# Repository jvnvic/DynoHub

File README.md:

# DynoHub - Automotive Development Platform

DynoHub is an ESP32-based development board in an Arduino Uno form factor, designed for automotive applications. It was developed at the Elektroniklabor F107 for the Fachhochschule Dortmund.

## Features

- **ESP32 WROOM** – Integrated WiFi and Bluetooth
- **Modular Automotive-grade power supply** – Wide input voltage range: 4.75V to 45V
- **CAN Bus** – Automotive communication support
- **100Mbit Ethernet** – High-speed wired networking
- **MicroSD Card Slot** – Expandable storage
- **Arduino Shield Compatibility** – Supports most Arduino shields
- **Stackable Design** – Multiple boards can be stacked and bridged with a single power and CAN input

## Getting Started

DynoHub is beginner-friendly and easy to set up. An **Arduino IDE Board Configuration** is available, along with dedicated **libraries** for each peripheral, complete with example sketches.

### Installing the DynoHub Board Package in Arduino IDE

To use the DynoHub board with Arduino IDE, you need to install the custom board package. Follow these steps:

1. Open **Arduino IDE**.
2. Go to **File** > **Preferences** (Windows) or **Arduino** > **Preferences** (Mac).
3. In the **Additional Board Manager URLs** field, add the following URL:

```text
https://raw.githubusercontent.com/jvnvic/DynoHub/refs/heads/main/Software/arduino-esp32-dynohub/hardware/FH%20Dortmund/package_dynohub_index.json
```

  If there are existing URLs, separate them with a comma.

5. Click **OK** to save the settings.
6. Open **Tools** > **Board** > **Boards Manager**.
7. Search for **DynoHub** and install the corresponding board package.
8. Once installed, select the appropriate **DynoHub** board from **Tools** > **Board**.

You are now ready to program your DynoHub board with Arduino IDE!

### Libraries & Examples
Libraries are available for:
- Ethernet: https://github.com/jvnvic/UDPSender
- SD Card: https://github.com/jvnvic/EasySDMMC

Each library comes with sample code to help you get started quickly.

## Diagrams

- **Pinout Diagram**  

- **Functional Schematic Block Diagram**  
  
## License
This project is open-source and available for personal and educational use.

---

Developed at **Elektroniklabor F107** – **Fachhochschule Dortmund**

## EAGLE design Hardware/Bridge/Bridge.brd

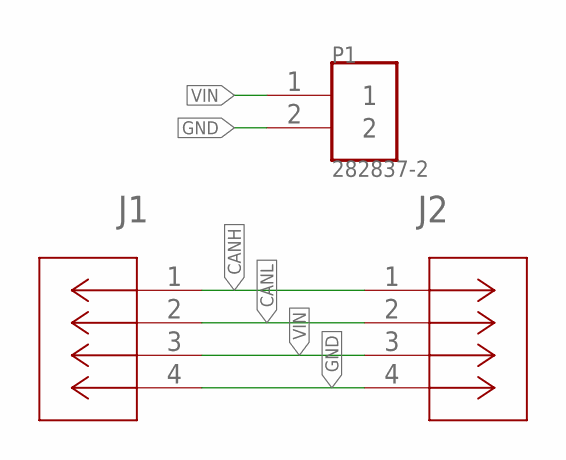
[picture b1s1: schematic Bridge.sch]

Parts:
J1, J2: 22027043CONN4X1_22027043_MOL; CONN4X1_22027043_MOL
P1: 282837-2; TE_282837-2

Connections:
CANH: J1.1, J2.1
CANL: J1.2, J2.2
GND: J1.4, J2.4, P1.2
VIN: J1.3, J2.3, P1.1

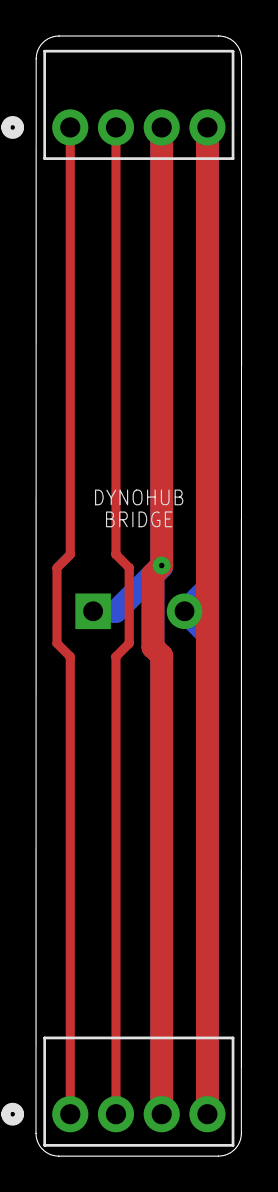
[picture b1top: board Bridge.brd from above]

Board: 2 copper layers, 11.4 x 62.2 mm, 3 parts (1 on the bottom side), 4 nets.

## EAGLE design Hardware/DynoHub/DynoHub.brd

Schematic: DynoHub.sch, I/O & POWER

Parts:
3.3V, 5V, 12V: C965807; CHIPLED_0603
C1, C4: 1uF; C0603
C2, C6, C7, C9, C20, C22, C29, C30, C33, C34, C35: 100nF; C0402K
C3: 4.7uF; C0402K
C5: 47uF; C0805
C8: 2.2uF; C0402K
C10, C103: 100 nF; C0402K
C19: 4.7uF; C0603
C21, C43: 1nF; C0402K
C23, C24: 22uF; C0603
C27, C28, C31, C32: 100nF; C0603
C107: 4.7nF 100V; C0603
C108, C109: 100pF 50V; C0603
CAN_TX: SJ
D6: BAT54C; SOT95P240X120-3N
D7: ESDS314DBVR; SOT95P280X145-5N
D8, D9: GG0402052R542P; DIONC1006X55N
D101: NUP2105LT1G; SOT96P237X111-3N
ETH_EN: SJ
F1: MF-FSML050_8-2; FUSC1608X70N
IC1: LMV321AIDBVR; SOT95P280X145-5N
IC2, IC6, IC7: TXB0108DQSR
IC3: USBLC6-2SC6; SOT95P280X145-6N
IC4: TLV1117LV33DCYR; SOT230P700X180-4N
IC9: ESP32-WROOM-32E-N8R2; ESP32WROOM32EN8R2
IC10: CP2102N-A02-GQFN28R; QFN50P500X500X80-29N
IC11: TS3L501ERUAR; QFN50P350X900X80-43N
J4: TYPE-C-31-M-12; HRO_TYPE-C-31-M-12
J5, J6: 1718570004CONN_SD-171857-0001_M265_04_MO; CONN_SD-171857-0001_M265_04_MO
J9: HR911105A; HANRUN_HR911105A
J-SD_DAT: SJ
JANALOG1: 6x1F-H8.5-L14.5mm; 1X06
JHIGH1: 10x1F-H8.5-L14.5mm; 1X10
JLOW1: 8x1F-H8.5-L14.5mm; 1X08
J_SD_CLK: SJ
J_SD_CMD: SJ
L1, L5: 600R 2A; L2012C
MICRO_SD1: TF-01A
POWER1: 8x1F-H8.5-L14.5mm; 1X08
Q1, Q2: SS8050-G; SOT95P240X115-3N
Q3: FDN340P; SOT95P237X112-3N
R1: 1M; R0603
R2, R3: 5K1; R0603
R4, R18, R19, R20, R28, R32, R49, R50, R51, R52, R57, R58: 2.2k; R0402
R5, R8, R29, R31, R35: 10k; R0603
R6: 47.5k 5%; R0402
R9: 470; R0603
R10: 22.1k 5%; R0402
R11: 100; R0603
R12: 15; R0603
R13: 2k 5%; R0402
R14, R15, R16: 10k 5%; R0402
R17, R22: 220; R0402
R21: 10; R0402
R23, R30, R55: 10k; R0402
R24, R25, R26, R27: 49,9 1%; R0402
R53, R54: 2.2k; R0603
R56: 12k 1%; R0402
R104: 47K; R0603
R107, R108: 59; R0603
R111: 10K; R0402
S3: EVP-AF5B70; EVPAF5B70
SJ1: SJ
U2: LAN8710A-EZC; QFN50P500X500X100-33N
U3: SN65HVD230; SOIC127P599X175-8N
U$1, U$2, U$3, U$4, U$5, U$6, U$7, U$13, U$14, U$15, U$16, U$17, U$18, U$19, U$20, U$21, U$22, U$23, U$24, U$25, U$26, U$27, U$28, U$29, U$30, U$31, U$32, U$33, U$34, U$35: NC
U$8, U$9, U$10, U$11, U$12: 2X3MM_PAD
Z1: BZX384C5V1-HE3-08; SOD2713X115N

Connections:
3V3: 3.3V.A, C2.1, C3.1, C4.1, C19.1, C20.1, C22.1, C23.1, C27.2, C29.2, C31.2, C35.2, C103.1, ETH_EN.1, IC1.4 (-IN), IC2.5 (VCCA), IC4.2 (OUTPUT_1), IC4.4 (OUTPUT_2), IC6.5 (VCCA), IC7.5 (VCCA), IC9.2 (3V3), IC10.6 (VDD), IC10.7 (VREGIN), IC11.39 (VDD_7), J9.9 (GA), L1.1, L5.1, POWER1.4, R4.2, R13.1, R18.2, R19.2, R20.2, R23.2, R28.2, R51.2, R52.2, R53.2, R54.2, R55.2, R111.2, U2.12 (VDDIO), U3.3 (VCC)
5V: 5V.A, C1.1, C28.2, C30.2, C32.2, IC1.5 (V+), IC2.16 (VCCB), IC4.3 (INPUT), IC6.16 (VCCB), IC7.16 (VCCB), POWER1.2, POWER1.5, Q3.2 (S), U$8.P$1
12V: 12V.A, POWER1.8, R8.2, U$9.P$1
!ETH_EN: ETH_EN.2, IC11.13 (SEL), R35.2
A0/ADC1_6/GPIO34: IC7.10 (A8), IC9.6 (IO34)
A0/ADC1_6/GPIO34_5V: IC7.11 (B8), JANALOG1.1
A1/ADC1_7/GPIO35: IC7.9 (A7), IC9.7 (IO35)
A1/ADC1_7/GPIO35_5V: IC7.12 (B7), JANALOG1.2
A2/ADC1_4/GPIO32: IC7.8 (A6), IC9.8 (IO32)
A2/ADC1_4/GPIO32_5V: IC7.13 (B6), JANALOG1.3
A3/ADC1_5/GPIO33: IC7.7 (A5), IC9.9 (IO33)
A3/ADC1_5/GPIO33_5V: IC7.14 (B5), JANALOG1.4
A4/TXCAN/ADC2_0/GPIO4: CAN_TX.1, IC7.4 (A4), IC9.26 (IO4)
A4/TXCAN/ADC2_0/GPIO4_5V: IC7.17 (B4), JANALOG1.5
A5/ADC2_2/SD_DAT0/GPIO2: D6.1 (A1), IC7.3 (A3), IC9.24 (IO2), J-SD_DAT.1
A5/ADC2_2/SD_DATO/GPIO2_5V: IC7.18 (B3), JANALOG1.6
AREF/GPI39: IC9.5 (SENSOR_VN), JHIGH1.8
CANGND_BF_C: C107.2, SJ1.1
CANH_P: C109.2, D101.2 (A_2), J5.4, J6.4, R108.1, U3.7 (CANH)
CANL_BF_JMP: R107.1, R108.2, SJ1.2
CANL_N: C108.2, D101.1 (A_1), J5.3, J6.3, R107.2, U3.6 (CANL)
CC1: J4.A5 (CC1), R3.2
CC2: J4.B5 (CC2), R2.2
CLK: MICRO_SD1.5 (CLK), R22.1
CMP: IC1.3 (+IN), R5.2, R8.1, Z1.1 (K)
CS/D10/GPIO5: IC6.8 (A6), IC9.29 (IO5)
CS/D10/GPIO5_5V: IC6.13 (B6), JHIGH1.3
D0/UART_RXD: IC2.10 (A8), IC9.34 (RXD0), IC10.25 (RXD)
D0/UART_RXD_5V: IC2.11 (B8), JLOW1.1
D1/UART_TXD: IC2.9 (A7), IC9.35 (TXD0), IC10.26 (TXD)
D1/UART_TXD_5V: IC2.12 (B7), JLOW1.2
D2/EMAC_RXD1/GPIO26: IC9.11 (IO26), IC11.3 (A1)
D2/GPIO26: IC2.8 (A6), IC11.35 (C1)
D2/GPIO26_5V: IC2.13 (B6), JLOW1.3
D3/EMAC_RXD0/GPIO25: IC9.10 (IO25), IC11.6 (A2)
D3/GPIO25: IC2.7 (A5), IC11.32 (C2)
D3/GPIO25_5V: IC2.14 (B5), JLOW1.4
D4/EMAC_CO180/GPIO17: IC9.28 (IO17), IC11.2 (A0)
D4/GPIO17: IC2.4 (A4), IC11.36 (C0)
D4/GPIO17_5V: IC2.17 (B4), JLOW1.5
D5/GPIO16: IC2.3 (A3), IC9.27 (IO16)
D5/GPIO16_5V: IC2.18 (B3), JLOW1.6
D6/EMAC_RX_CRS_DV/GPIO27: IC9.12 (IO27), IC11.7 (A3)
D6/GPIO27: IC2.2 (A2), IC11.31 (C3)
D6/GPIO27_5V: IC2.19 (B2), JLOW1.7
D7/SD_CLK/GPIO14: IC2.1 (A1), IC9.13 (IO14), J_SD_CLK.1
D7/SD_CLK/GPIO14_5V: IC2.20 (B1), JLOW1.8
D8/GPIO12: IC6.10 (A8), IC9.14 (IO12)
D8/GPIO12_5V: IC6.11 (B8), JHIGH1.1
D9/GPIO13: IC6.9 (A7), IC9.16 (IO13)
D9/GPIO13_5V: IC6.12 (B7), JHIGH1.2
DAT0: MICRO_SD1.7 (DAT0), R21.1
DAT1: MICRO_SD1.8 (DAT1), R4.1
DAT2: MICRO_SD1.1 (DAT2), R20.1
DAT3: MICRO_SD1.2 (CD/DAT3), R19.1
EMAC_CO180: IC11.38 (B0), U2.5 (XTAL1/CLKIN)
EMAC_MDC: IC11.28 (B5), U2.17 (MDC)
EMAC_MDIO: IC11.29 (B4), R53.1, U2.16 (MDIO)
EMAC_RXD0: IC11.34 (B2), R51.1, U2.11 (RXD0/MODE0)
EMAC_RXD1: IC11.37 (B1), R52.1, U2.10 (RXD1/MODE1)
EMAC_RX_CRS_DV: IC11.33 (B3), R54.1, U2.15 (COL/CRS_DV/MODE2)
EMAC_TXD0: IC11.24 (B7), U2.22 (TXD0)
EMAC_TXD1: IC11.17 (LED__B0), U2.23 (TXD1)
EMAC_TX_EN: IC11.25 (B6), U2.21 (TXEN)
ESP_EN: C6.1, C10.1, IC9.3 (EN), POWER1.3, Q1.3 (C), R111.1, S3.A1 (NO_1), S3.A2 (NO_2)
ETH_LED_G: J9.10 (GC), R57.2
ETH_LED_Y: J9.12 (YA), R58.2
ETH_VDDCR: C7.1, C8.1, U2.6 (VDDCR)
GND: C1.2, C2.2, C3.2, C4.2, C5.1, C6.2, C7.2, C8.2, C9.2, C10.2, C19.2, C20.2, C21.2, C22.2, C23.2, C24.2, C27.1, C28.1, C29.1, C30.1, C31.1, C32.1, C33.2, C34.2, C35.1, C43.2, C103.2, C107.1, C108.1, C109.1, D7.2 (GND), D101.3 (A_3), IC1.2 (V-), IC2.15 (GND), IC3.2 (GND), IC4.1 (GND), IC6.15 (GND), IC7.15 (GND), IC9.1 (GND_1), IC9.15 (GND_2), IC9.38 (GND_3), IC9.39 (GND_4), IC9.40 (GND_5), IC9.41 (GND_6), IC9.42 (GND_7), IC9.43 (GND_8), IC9.44 (GND_9), IC9.45 (GND_10), IC9.46 (GND_11), IC9.47 (GND_12), IC10.3 (GND_1), IC10.29 (GND_2), IC11.5 (PD), IC11.43 (GND), J4.A1_B12 (GND), J4.B1_A12 (GND), J5.1, J6.1, J9.8 (GND), J9.11 (YC), JHIGH1.7, MICRO_SD1.6 (VSS), MICRO_SD1.MP1 (SHIELD), MICRO_SD1.MP2 (SHIELD), MICRO_SD1.MP3 (SHIELD), MICRO_SD1.MP4 (SHIELD), POWER1.6, POWER1.7, R1.1, R2.1, R3.1, R5.1, R6.1, R9.1, R11.1, R12.1, R14.1, R29.1, R30.1, R31.1, R32.2, R35.1, R49.2, R50.2, R56.1, R104.1, S3.B1 (COM_1), S3.B2 (COM_2), U2.24 (TXD2), U2.25 (TXD3), U2.33 (VSS), U3.2 (GND), U$11.P$1, U$12.P$1, Z1.2 (A)
GPIO0: D6.2 (A2), IC9.25 (IO0), Q2.3 (C), R17.2
MISO/D12/EMAC_TXD0/GPIO19: IC9.31 (IO19), IC11.12 (A7)
MISO/D12/GPIO19: IC6.4 (A4), IC11.22 (C7)
MISO/D12/GPIO19_5V: IC6.17 (B4), JHIGH1.5
MOSI/D11/EMAC_MDC/GPIO23: IC9.37 (IO23), IC11.10 (A5)
MOSI/D11/GPIO23: IC6.7 (A5), IC11.26 (C5)
MOSI/D11/GPIO23_5V: IC6.14 (B5), JHIGH1.4
unnamed: J4.S1 (SHIELD), J4.S2 (SHIELD), J4.S3 (SHIELD), J4.S4 (SHIELD), R1.2
unnamed: IC10.9 (RSTB), R13.2
unnamed: IC10.11 (SUSPENDB), R14.2
unnamed: Q1.1 (B), R16.1
unnamed: 12V.C, R9.2
unnamed: R104.2, U3.8 (RS)
unnamed: IC1.1 (OUT), Q3.1 (G)
unnamed: Q2.1 (B), R15.1
unnamed: D6.3 (CC), R17.1
unnamed: 5V.C, R11.2
unnamed: 3.3V.C, R12.2
unnamed: C21.1, J9.15 (SHIELD), J9.16 (SHIELD)
unnamed: F1.1, J4.A4_B9 (VBUS), J4.B4_A9 (VBUS)
unnamed: R28.1, U2.9 (RXD2/RMIISEL)
unnamed: R32.1, U2.8 (RXD3/PHYAD2)
unnamed: R49.1, U2.13 (RXER/RXD4/PHYAD0)
unnamed: R50.1, U2.7 (RXCLK/PHYAD1)
unnamed: C43.1, R55.1, U2.19 (NRST)
unnamed: R56.2, U2.32 (RBIAS)
unnamed: R58.1, U2.3 (LED1/REGOFF)
unnamed: R57.1, U2.2 (LED2/NINTSEL)
OE_A: IC2.6 (OE), R29.2
OE_B: IC6.6 (OE), R30.2
OE_C: IC7.6 (OE), R31.2
PC0: IC7.1 (A1)
PC0O: IC7.20 (B1)
PC1: IC7.2 (A2)
PC1O: IC7.19 (B2)
PHY_VDD: C9.1, C24.1, C33.1, C34.1, J9.4, J9.5, L5.2, R24.2, R25.2, R26.2, R27.2, U2.1 (VDD2A), U2.27 (VDD1A)
RXCAN/GPI36: IC9.4 (SENSOR_VP), U3.4 (R)
RX_N: D7.3 (I/O2), D9.1, J9.1 (TD+), R27.1, U2.30 (RXN)
RX_P: D7.1 (I/O1), D9.2, J9.3 (RD+), R25.1, U2.31 (RXP)
SCK/D13/EMAC_MDIO/GPIO18: IC9.30 (IO18), IC11.9 (A4)
SCK/D13/GPIO18: IC6.3 (A3), IC11.27 (C4)
SCK/D13/GPIO18_5V: IC6.18 (B3), JHIGH1.6
SCL/EMAC_TXD1/GPIO22: IC9.36 (IO22), IC11.15 (LED_A0)
SCL/GPIO22: IC6.1 (A1), IC11.19 (LED_C0)
SCL/GPIO22_5V: IC6.20 (B1), JHIGH1.10
SDA/EMAC_TX_EN/GPIO21: IC9.33 (IO21), IC11.11 (A6)
SDA/GPIO21: IC6.2 (A2), IC11.23 (C6)
SDA/GPIO21_5V: IC6.19 (B2), JHIGH1.9
SD_CLK/GPIO14_S: J_SD_CLK.2, R22.2
SD_CMD/GPIO15: IC9.23 (IO15), J_SD_CMD.1
SD_CMD/GPIO15_S: J_SD_CMD.2, MICRO_SD1.3 (CMD), R23.1
SD_DAT0/GPIO2_S: J-SD_DAT.2, R18.1, R21.2
TXCAN: CAN_TX.2, U3.1 (D)
TX_N: D7.4 (I/O3), D8.2, J9.2 (TD-), R26.1, U2.28 (TXN)
TX_P: D7.5 (I/O4), D8.1, J9.6 (RD-), R24.1, U2.29 (TXP)
USB_CTS: IC10.23 (CTS)
USB_DATA_CON_N: IC3.6 (I/O1_2), J4.A7 (DN1), J4.B7 (DN2)
USB_DATA_CON_P: IC3.4 (I/O2_2), J4.A6 (DP1), J4.B6 (DP2)
USB_DATA_N: IC3.1 (I/O1_1), IC10.5 (D-)
USB_DATA_P: IC3.3 (I/O2_1), IC10.4 (D+)
USB_DCD: IC10.1 (DCD)
USB_DSR: IC10.27 (DSR)
USB_DTR: IC10.28 (DTR), Q2.2 (E), R16.2
USB_RI: IC10.2 (RI_/_CLK)
USB_RTS: IC10.24 (RTS), Q1.2 (E), R15.2
VBUS: F1.2, IC3.5 (VBUS), IC10.8 (VBUS), Q3.3 (D), R6.2, R10.1, R10.2
VDD: C5.2, L1.2, MICRO_SD1.4 (VDD)
VIN: J5.2, J6.2, U$10.P$1

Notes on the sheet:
Auto program DTR RTS-->EN IO0 1 1 1 1 0 0 1 1 1 0 0 1 0 1 1 0
Pulldown OE nochmal prüfen
The PHY is set up as follows: MODE: All capable(10/100Base) -Auto-negotiation enabled -RMII Configuration -SMI address: 0x00
SEL
Function
A -> B
A -> C
Disconnect
Turn on S1 to deactivate Ethernet
limit cmp to 5.1V
7V-30V input

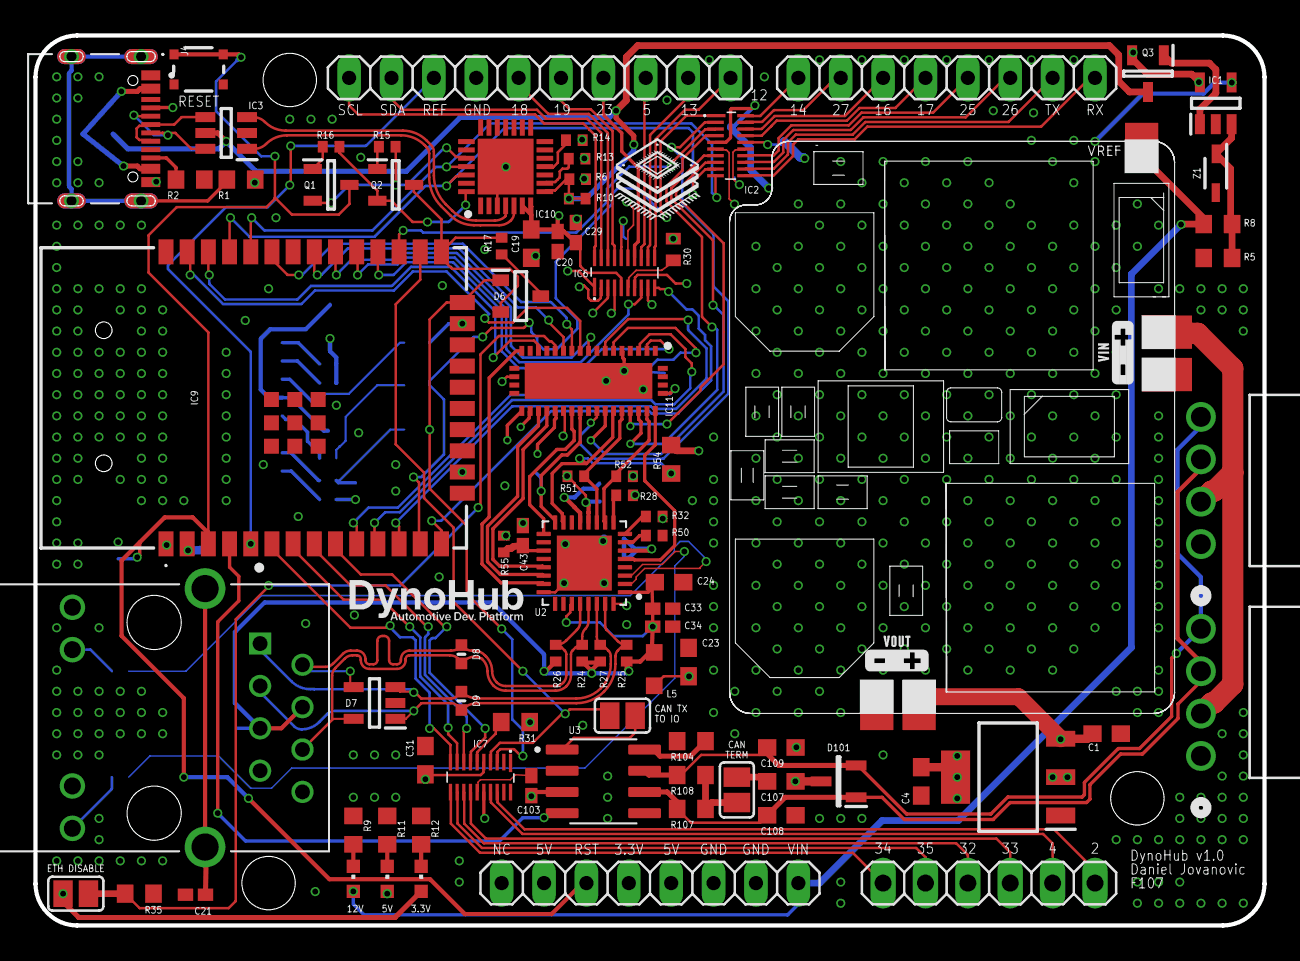
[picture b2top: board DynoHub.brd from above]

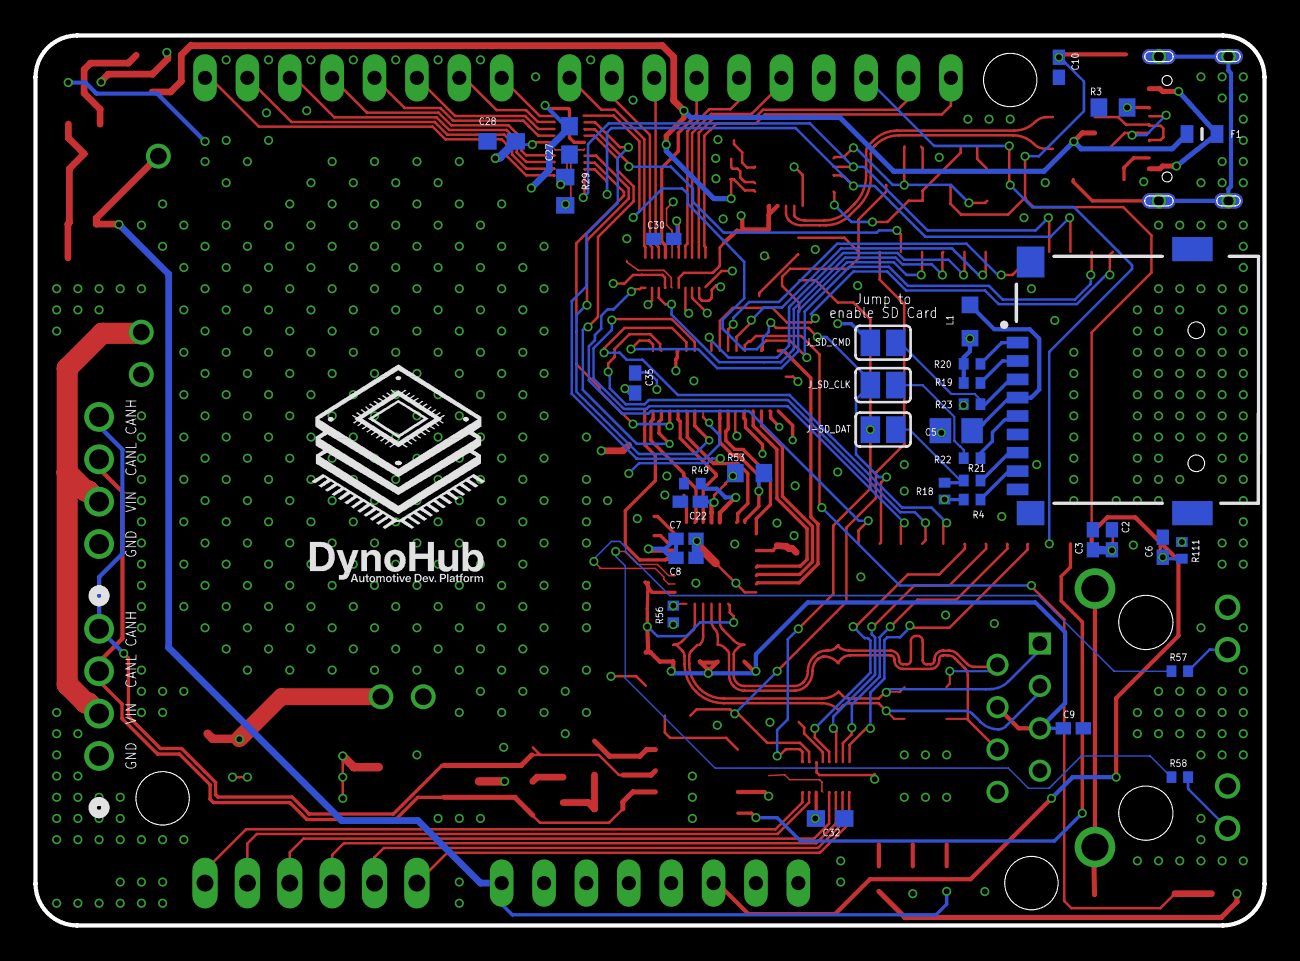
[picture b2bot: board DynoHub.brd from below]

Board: 4 copper layers, 73.7 x 53.3 mm, 153 parts (35 on the bottom side), 129 nets.

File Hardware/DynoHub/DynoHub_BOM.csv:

Comment,Designator,Footprint,LCSC Part #
1M,R1,R0603,C22935
1nF,C21 C43,C0402,C1523
1uF,C1 C4,C0603,C15849
2.2k,R28 R32 R50 R51 R52,R0402,C25879
2.2k,R54,R0603,C4190
2k 5%,R13,R0402,C4109
4.7nF 100V,C107,C0603,C12164
4.7uF,C19,C0603,C19666
5K1,R2,R0603,C23186
10k,R5 R8,R0603,C25804
10k,R30,R0402,C25744
10k,R31 R35,R0603,C25804
10k,R55,R0402,C25744
10k 5%,R14 R15 R16,R0402,C25744
15,R12,R0603,C22810
22.1k 5%,R10,R0402,C43473
22uF,C23 C24,C0603,C59461
47.5k 5%,R6,R0402,C25896
47K,R104,R0603,C25819
49 9 1%,R24,R0402,C25120
49 9 1%,R25,R0402,C25120
49 9 1%,R26,R0402,C25120
49 9 1%,R27,R0402,C25120
59,R107 R108,R0603,C23086
100,R11,R0603,C22775
100 nF,C103,C0402,C1525
100nF,C20 C29,C0402,C1525
100nF,C31,C0603,C14663
100nF,C33 C34,C0402,C1525
100pF 50V,C108 C109,C0603,C14858
220,R17,R0402,C25091
470,R9,R0603,C23179
600R 2A,L5,L2012C,C3716677
BAT54C,D6,SOT95P240X120-3N,C916424
BZX384C5V1-HE3-08,Z1,SOD2713X115N,C232203
C965807,3.3V 5V 12V,CHIPLED_0603,C965807
CP2102N-A02-GQFN28R,IC10,QFN50P500X500X80-29N,C964632
ESDS314DBVR,D7,SOT95P280X145-5N,C1847859
ESP32-WROOM-32E-N8R2,IC9,ESP32WROOM32EN8R2,C5361945
EVP-AF5B70,S3,EVPAF5B70,C79148
FDN340P,Q3,SOT95P237X112-3N,C75469
GG0402052R542P,D8 D9,DIONC1006X55N,C1973257
LAN8710A-EZC,U2,QFN50P500X500X100-33N,C46185
LMV321AIDBVR,IC1,SOT95P280X145-5N,C484730
NUP2105LT1G,D101,SOT96P237X111-3N,C2890118
SN65HVD230,U3,SOIC127P599X175-8N,C12084
SS8050-G,Q1 Q2,SOT95P240X115-3N,C164886
TLV1117LV33DCYR,IC4,SOT230P700X180-4N,C15578
TS3L501ERUAR,IC11,QFN50P350X900X80-43N,C2652454
TXB0108DQSR,IC2 IC6 IC7,TXB0108DQSR,C427057
TYPE-C-31-M-12,J4,HRO_TYPE-C-31-M-12,C165948
USBLC6-2SC6,IC3,SOT95P280X145-6N,C7519
2.2k,R4 R18 R19 R20 R49,R0402,C25879
2.2k,R53,R0603,C4190
2.2k,R57 R58,R0402,C25879
2.2uF,C8,C0402,C12530
4.7uF,C3,C0402,C23733
5K1,R3,R0603,C23186
10,R21,R0402,C25077
10K,R111,R0402,C25744
10k,R23,R0402,C25744
10k,R29,R0603,C25804
12k 1%,R56,R0402,C25752
47uF,C5,C0805,C16780
100 nF,C10,C0402,C1525
100nF,C2 C6 C7 C9 C22,C0402,C1525
100nF,C27 C28,C0603,C14663
100nF,C30,C0402,C1525
100nF,C32,C0603,C14663
100nF,C35,C0402,C1525
220,R22,R0402,C25091
600R 2A,L1,L2012C,C3716677
MF-FSML050_8-2,F1,FUSC1608X70N,C2844464
TF-01A,MICRO_SD1,TF-01A,C91145
HR911105A,LAN,HR911105A,C12074

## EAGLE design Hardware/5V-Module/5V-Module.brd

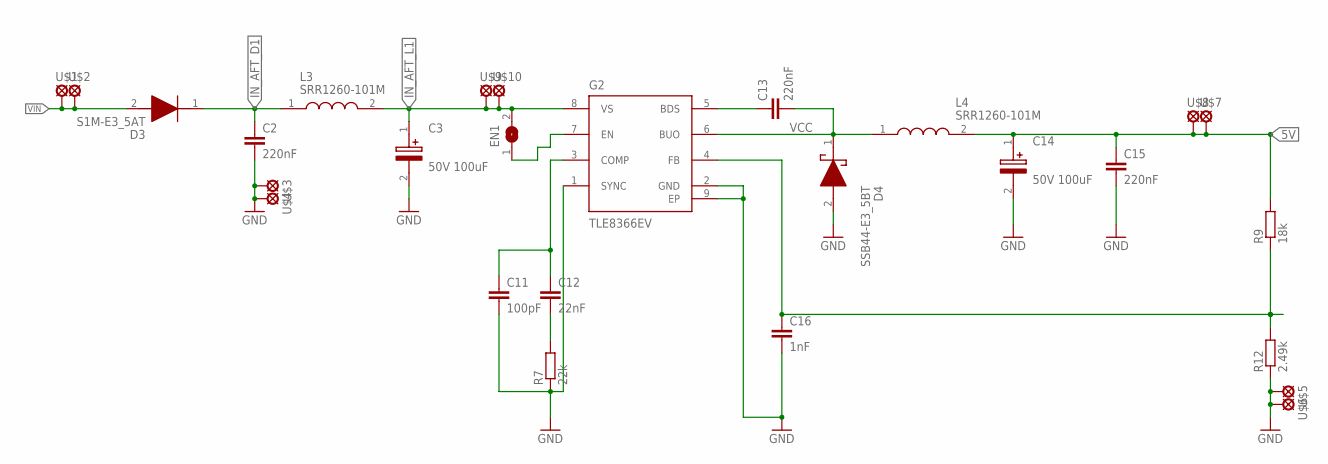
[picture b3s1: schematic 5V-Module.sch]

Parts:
C2, C13, C15: 220nF; C0603
C3, C14: 50V 100uF; CAPAE830X1050N
C11: 100pF; C0603
C12: 22nF; C0603
C16: 1nF; C0603
D3: S1M-E3_5AT; DIOM5127X229N
D4: SSB44-E3_5BT; DIOM5436X244N
EN1: SJ
G2: TLE8366EV; SOIC127P600X170-9N-1
L3, L4: SRR1260-101M; SRR1260101M
R7: 22k; R0603
R9: 18k; R0603
R12: 2.49k; R0603
U$1, U$2, U$3, U$4, U$5, U$6, U$7, U$8, U$9, U$10: 2MM_PAD

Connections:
5V: C14.1 (+), C15.1, L4.2, R9.2, U$7.P$1, U$8.P$1
GND: C2.2, C3.2 (-), C11.2, C14.2 (-), C15.2, C16.2, D4.2 (A), G2.1 (SYNC), G2.2 (GND), G2.9 (EP), R7.1, R12.1, U$3.P$1, U$4.P$1, U$5.P$1, U$6.P$1
IN_AFT_D1: C2.1, D3.1 (K), L3.1
IN_AFT_L1: C3.1 (+), EN1.2, G2.8 (VS), L3.2, U$9.P$1, U$10.P$1
unnamed: C11.1, C12.1, G2.3 (COMP)
unnamed: C12.2, R7.2
unnamed: C13.1, G2.5 (BDS)
unnamed: C16.1, G2.4 (FB), R9.1, R12.2
unnamed: EN1.1, G2.7 (EN)
VCC: C13.2, D4.1 (K), G2.6 (BUO), L4.1
VIN: D3.2 (A), U$1.P$1, U$2.P$1

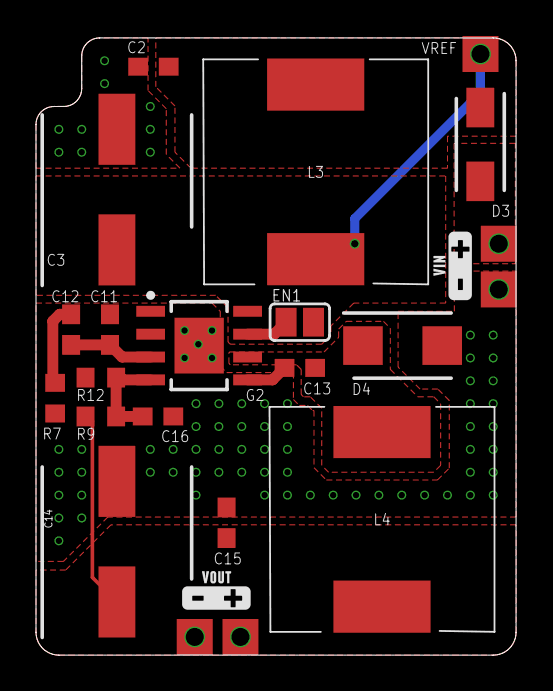
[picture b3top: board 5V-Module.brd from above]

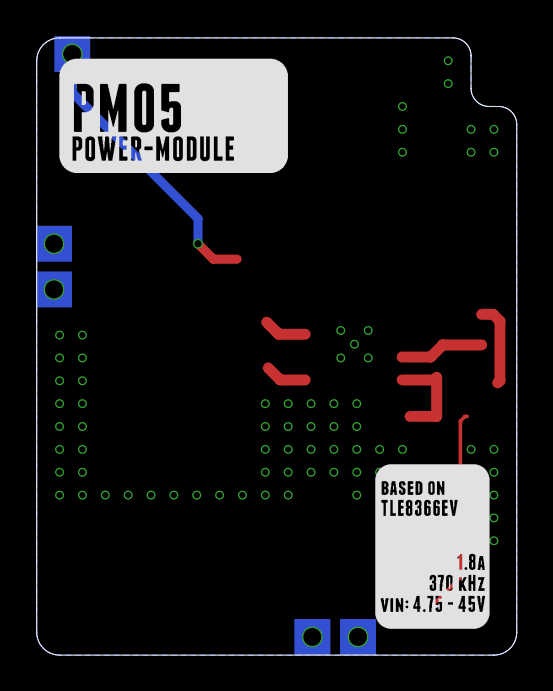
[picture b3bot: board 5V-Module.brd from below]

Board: 2 copper layers, 26.7 x 34.3 mm, 27 parts (5 on the bottom side), 11 nets.

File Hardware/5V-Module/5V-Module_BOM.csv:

Comment,Designator,Footprint,LCSC Part #
1nF,C16,C0603,C1588
2.49k,R12,R0603,C108190
18k,R9,R0603,C25810
22k,R7,R0603,C31850
22nF,C12,C0603,C21122
50V 100uF,C3 C14,CAPAE830X1050N,C2983307
100pF,C11,C0603,C14858
220nF,C2 C13 C15,C0603,C21120
S1M-E3_5AT,D3,DIOM5127X229N,C968552
SRR1260-101M,L3 L4,SRR1260101M,C5127262
SSB44-E3_5BT,D4,DIOM5436X244N,C151740

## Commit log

2025-03-06 push board package
2025-03-06 Changed paths
2025-03-06 updated board package
2025-03-06 board package update
2025-03-06 removed hash
2025-03-06 updated board info
2025-03-06 push libs
2025-03-06 updated board
2025-03-06 updated index
2025-03-06 updated hash
2025-03-06 updated board config
2025-03-07 pushed diagrams

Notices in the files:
parts and their libraries:
COPYRIGHT: Copyright (C) 2025 Ultra Librarian. All rights reserved.
